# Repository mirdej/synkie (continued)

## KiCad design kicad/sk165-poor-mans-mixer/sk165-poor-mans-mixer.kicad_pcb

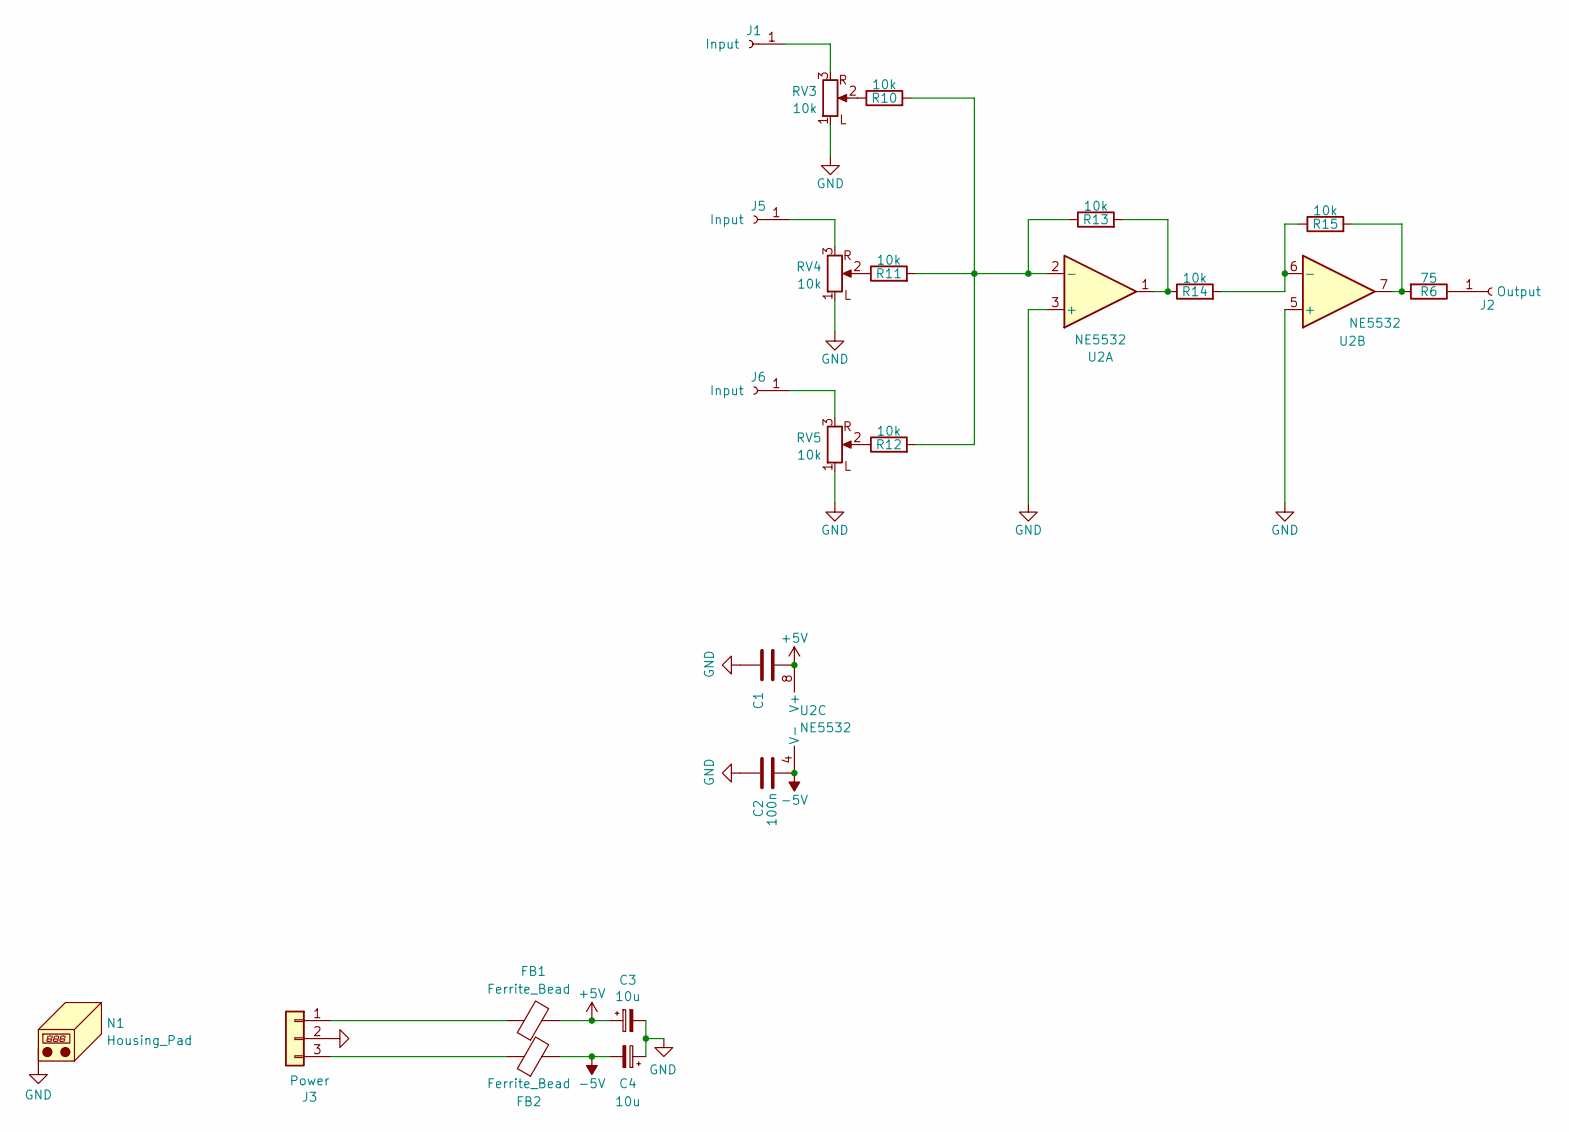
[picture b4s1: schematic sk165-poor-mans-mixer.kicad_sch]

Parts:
C1, C2: 100n; C_0402_1005Metric; LCSC C1525
C3, C4: 10u; C_0805_2012Metric; LCSC C15850
FB1, FB2: Ferrite_Bead; L_0805_2012Metric; LCSC C1017
J1, J5, J6: Input; Banana2mm-Löthülse
J2: Output; Banana2mm-Löthülse
J3: Power; Molex_KK-254_AE-6410-03A_1x03_P2.54mm_Vertical_SMD
N1: Housing_Pad; Frontplate_10mm
R6: 75; R_0603_1608Metric; LCSC C4275
R10, R11, R12, R13, R14, R15: 10k; R_0603_1608Metric; LCSC C25804
RV3, RV4, RV5: 10k; Alps_RK097_Frontplate
U2: NE5532; SOIC-8_3.9x4.9mm_P1.27mm; LCSC C7426

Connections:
+5V: C1.2, C3.1, FB1.2, U2.8 (V+)
-5V: C2.2, C4.2, FB2.2, U2.4 (V-)
GND: C1.1, C2.1, C3.2, C4.1, J3.2, N1.1 (PAD_1), RV3.1 (L), RV4.1 (L), RV5.1 (L), U2.3 (+), U2.5 (+)
unnamed: J1.1 (Pin_1_1), RV3.3
unnamed: J2.1 (Pin_1_1), R6.1
unnamed: FB1.1, J3.1
unnamed: FB2.1, J3.3
unnamed: J5.1 (Pin_1_1), RV4.3
unnamed: J6.1 (Pin_1_1), RV5.3
unnamed: R10.1, RV3.2
unnamed: R11.1, RV4.2
unnamed: R12.1, RV5.2
unnamed: R13.2, R14.1, U2.1
unnamed: R6.2, R15.2, U2.7
unnamed: R10.2, R11.2, R12.2, R13.1, U2.2 (-)
unnamed: R14.2, R15.1, U2.6 (-)

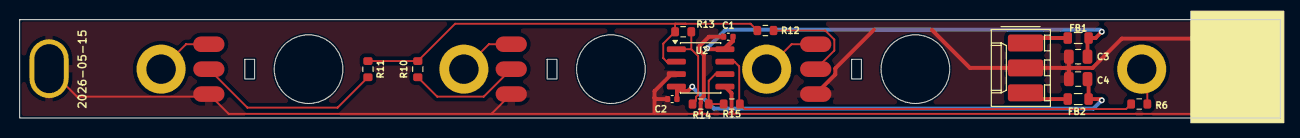
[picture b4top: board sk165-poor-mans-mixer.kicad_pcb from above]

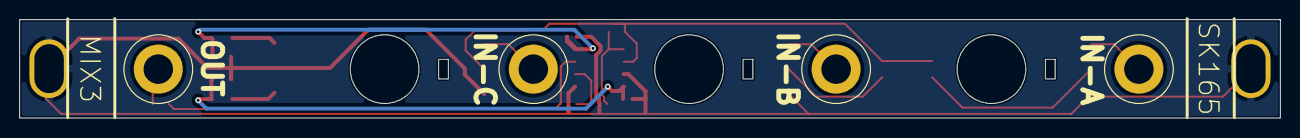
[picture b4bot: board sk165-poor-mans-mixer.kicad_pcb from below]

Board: 2 copper layers, 128.5 x 10.0 mm, 23 parts (8 on the bottom side), 16 nets.
